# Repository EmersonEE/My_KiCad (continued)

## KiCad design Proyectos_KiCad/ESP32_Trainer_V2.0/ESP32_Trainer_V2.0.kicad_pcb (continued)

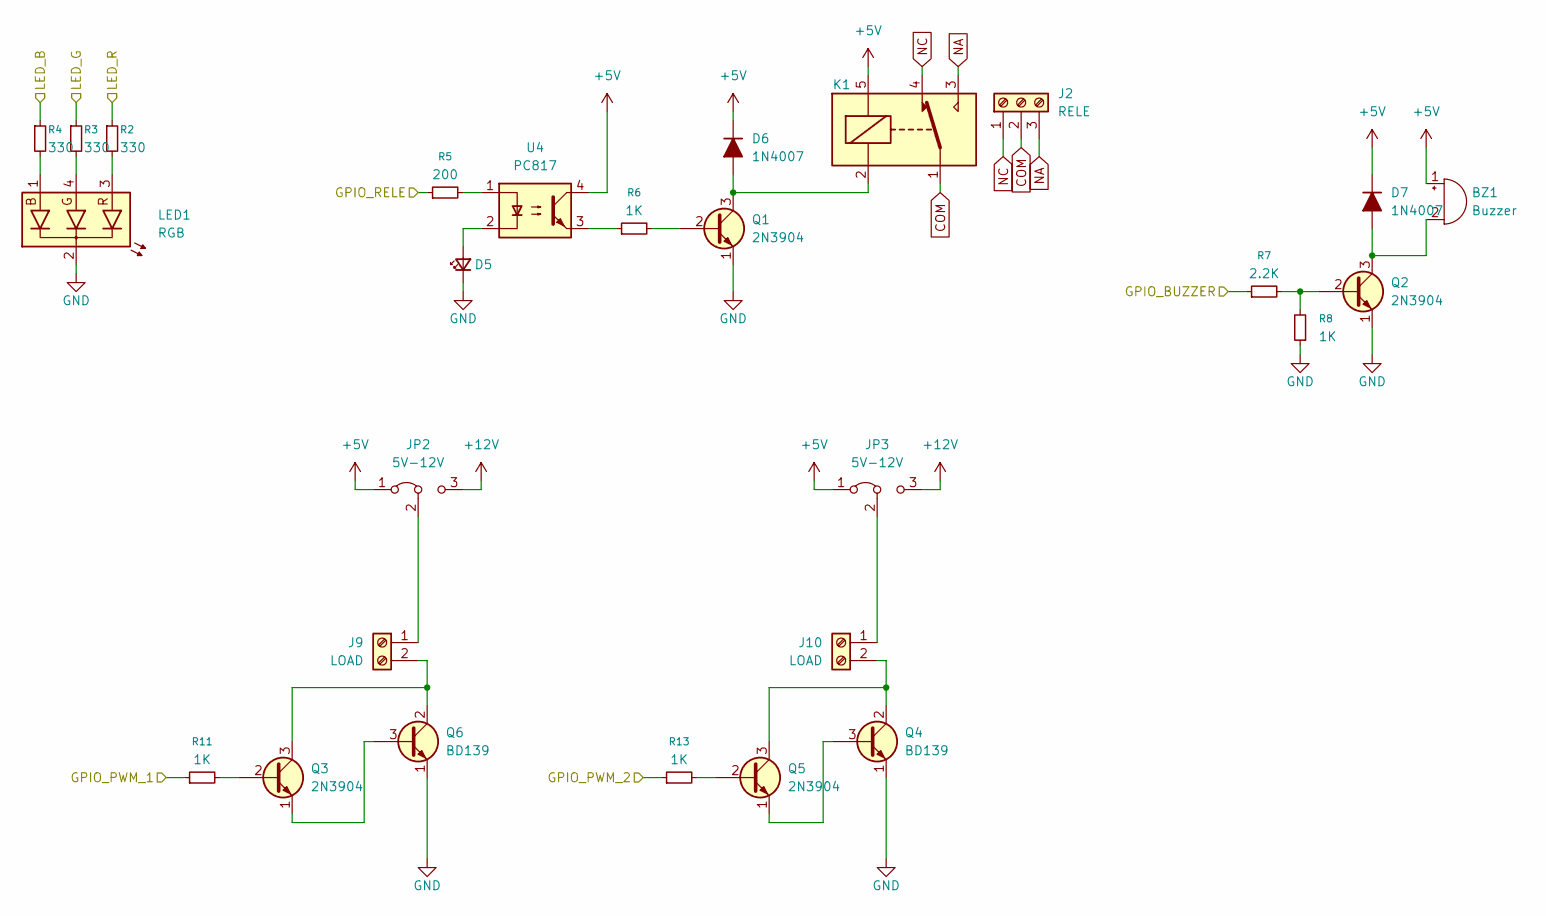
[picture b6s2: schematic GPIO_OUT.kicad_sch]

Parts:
BZ1: Buzzer; Buzzer_12x9.5RM7.6
D5: LED_OPTO; LED_D3.0mm
D6: 1N4007; D_DO-41_SOD81_P7.62mm_Horizontal
D7: 1N4007; D_SMA_BigPads
J2: RELE; TerminalBlock_Phoenix_MKDS-1,5-3-5.08_1x03_P5.08mm_Horizont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
J9, J10: LOAD; TerminalBlock_Phoenix_MKDS-1,5-2-5.08_1x02_P5.08mm_Horizont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
JP2, JP3: 5V-12V; PinHeader_1x03_P2.54mm_Vertical
K1: SANYOU_SRD_Form_C; Relay_SPDT_SANYOU_SRD_Series_Form_C
LED1: RGB; LED_D5.0mm-4_RGB_Wide_Pins
Q1, Q2, Q3, Q5: 2N3904; SOT-23W_BigPads
Q4, Q6: BD139; TO-126-3_Vertical_ECB
R2, R3, R4: 330; R_0805_2012Metric_Pad1.15x1.40mm
R5: 200; R_0805_2012Metric_Pad1.15x1.40mm
R6, R8, R11, R13: 1K; R_0805_2012Metric_Pad1.15x1.40mm
R7: 2.2K; R_0805_2012Metric_Pad1.15x1.40mm
U4: PC817; DIP-4_W7.62mm_LongPads

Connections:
+5V: BZ1.1 (+), D6.1 (K), D7.1 (K), JP2.1 (A), JP3.1 (A), K1.5, U4.4; also elsewhere on the board
+12V: JP2.3 (B), JP3.3 (B); also elsewhere on the board
/ESP32/GPIO_BUZZER: R7.1; also elsewhere on the board
/ESP32/GPIO_PWM_1: R11.1; also elsewhere on the board
/ESP32/GPIO_PWM_2: R13.1; also elsewhere on the board
/ESP32/GPIO_RELE: R5.1; also elsewhere on the board
/ESP32/LED_B: R4.1; also elsewhere on the board
/ESP32/LED_G: R3.1; also elsewhere on the board
/ESP32/LED_R: R2.1; also elsewhere on the board
COM: J2.2, K1.1
GND: D5.1 (K), LED1.2 (A), Q1.1 (E), Q2.1 (E), Q4.1 (E), Q6.1 (E), R8.1; also elsewhere on the board
NA: J2.3, K1.3
NC: J2.1, K1.4
unnamed: BZ1.2 (-), D7.2 (A), Q2.3 (C)
unnamed: D5.2 (A), U4.2
unnamed: D6.2 (A), K1.2, Q1.3 (C)
unnamed: J9.1, JP2.2 (C)
unnamed: J9.2, Q3.3 (C), Q6.2 (C)
unnamed: J10.1, JP3.2 (C)
unnamed: J10.2, Q4.2 (C), Q5.3 (C)
unnamed: LED1.1 (B), R4.2
unnamed: LED1.4 (G), R3.2
unnamed: LED1.3 (R), R2.2
unnamed: Q1.2 (B), R6.2
unnamed: Q2.2 (B), R7.2, R8.2
unnamed: Q3.2 (B), R11.2
unnamed: Q3.1 (E), Q6.3 (B)
unnamed: Q4.3 (B), Q5.1 (E)
unnamed: Q5.2 (B), R13.2
unnamed: R5.2, U4.1
unnamed: R6.1, U4.3

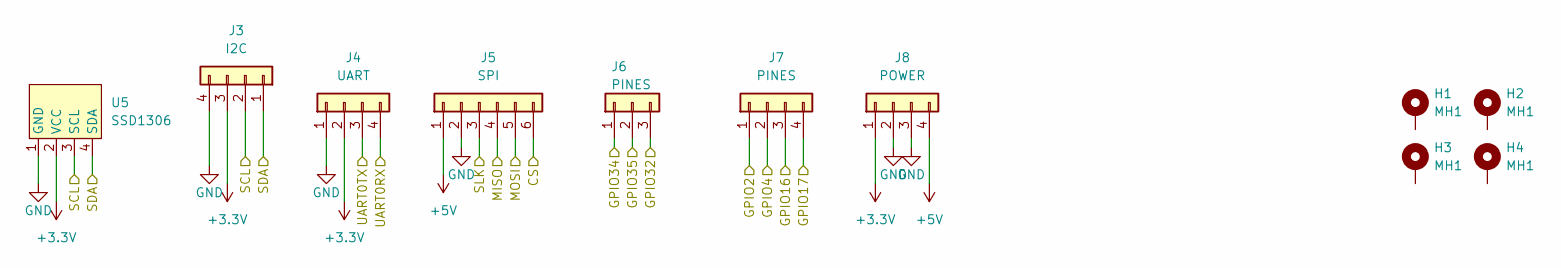
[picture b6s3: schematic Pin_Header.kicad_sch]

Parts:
H1, H2, H3, H4: MH1; MountingHole_3.2mm_M3_Pad_Via
J3: I2C; PinHeader_1x04_P2.54mm_Horizontal
J4: UART; PinHeader_1x04_P2.54mm_Vertical
J5: SPI; PinHeader_1x06_P2.54mm_Vertical
J6: PINES; PinHeader_1x03_P2.54mm_Vertical
J7: PINES; PinHeader_1x04_P2.54mm_Vertical
J8: POWER; PinHeader_1x04_P2.54mm_Vertical
U5: SSD1306

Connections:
+3.3V: J3.3, J4.2, J8.1, U5.2 (VCC); also elsewhere on the board
+5V: J5.1, J8.4; also elsewhere on the board
/ESP32/CLK: J5.3; also elsewhere on the board
/ESP32/CS: J5.6; also elsewhere on the board
/ESP32/GPIO2: J7.1; also elsewhere on the board
/ESP32/GPIO4: J7.2; also elsewhere on the board
/ESP32/GPIO16: J7.3; also elsewhere on the board
/ESP32/GPIO17: J7.4; also elsewhere on the board
/ESP32/GPIO32: J6.3; also elsewhere on the board
/ESP32/GPIO34: J6.1; also elsewhere on the board
/ESP32/GPIO35: J6.2; also elsewhere on the board
/ESP32/MISO: J5.4; also elsewhere on the board
/ESP32/MOSI: J5.5; also elsewhere on the board
/ESP32/SCL: J3.2, U5.3 (SCL); also elsewhere on the board
/ESP32/SDA: J3.1, U5.4 (SDA); also elsewhere on the board
/ESP32/UART0RX: J4.4; also elsewhere on the board
/ESP32/UART0TX: J4.3; also elsewhere on the board
GND: J3.4, J4.1, J5.2, J8.2, J8.3, U5.1 (GND); also elsewhere on the board

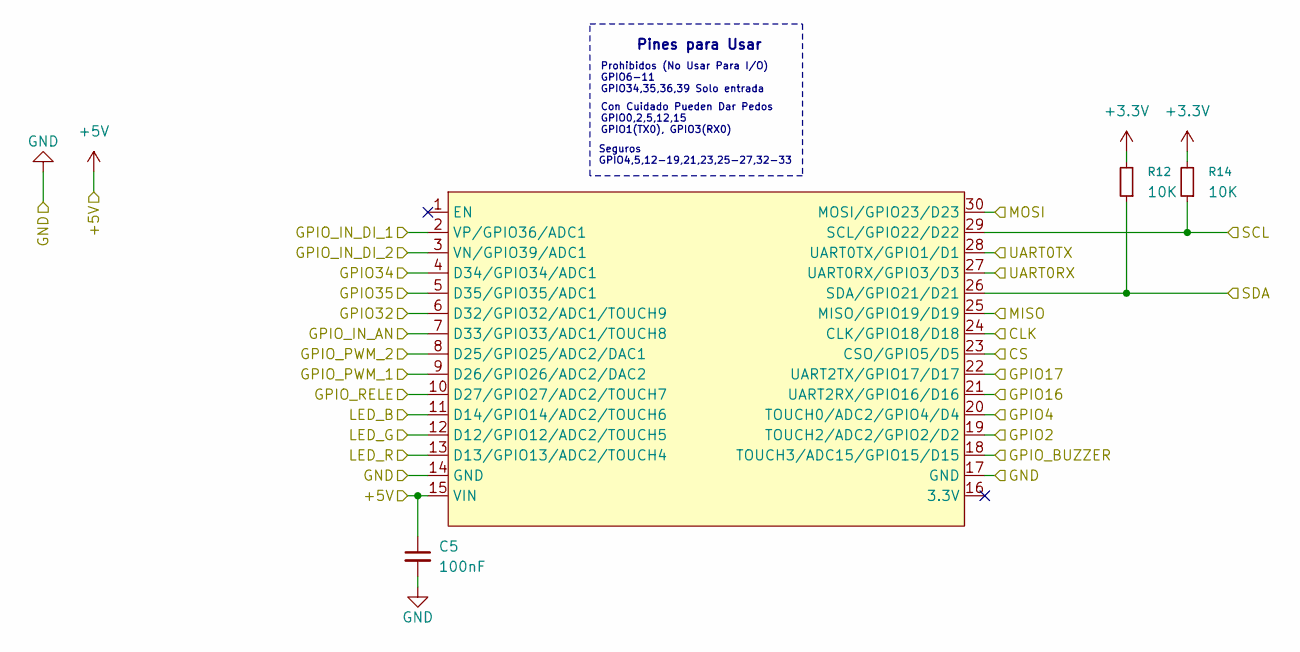
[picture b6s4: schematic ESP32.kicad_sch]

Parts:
C5: 100nF; C_Disc_D4.3mm_W1.9mm_P5.00mm
R12, R14: 10K; R_0805_2012Metric_Pad1.15x1.40mm
U3: ESP32_DevKit_V1_DOIT; ESP32_DEVKIT_V1_E32

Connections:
+3.3V: R12.2, R14.2; also elsewhere on the board
+5V: C5.1, U3.15 (VIN); also elsewhere on the board
/ESP32/CLK: U3.24 (CLK/GPIO18/D18); also elsewhere on the board
/ESP32/CS: U3.23 (CSO/GPIO5/D5); also elsewhere on the board
/ESP32/GPIO2: U3.19 (TOUCH2/ADC2/GPIO2/D2); also elsewhere on the board
/ESP32/GPIO4: U3.20 (TOUCH0/ADC2/GPIO4/D4); also elsewhere on the board
/ESP32/GPIO16: U3.21 (UART2RX/GPIO16/D16); also elsewhere on the board
/ESP32/GPIO17: U3.22 (UART2TX/GPIO17/D17); also elsewhere on the board
/ESP32/GPIO32: U3.6 (D32/GPIO32/ADC1/TOUCH9); also elsewhere on the board
/ESP32/GPIO34: U3.4 (D34/GPIO34/ADC1); also elsewhere on the board
/ESP32/GPIO35: U3.5 (D35/GPIO35/ADC1); also elsewhere on the board
/ESP32/GPIO_BUZZER: U3.18 (TOUCH3/ADC15/GPIO15/D15); also elsewhere on the board
/ESP32/GPIO_IN_AN: U3.7 (D33/GPIO33/ADC1/TOUCH8); also elsewhere on the board
/ESP32/GPIO_IN_DI_1: U3.2 (VP/GPIO36/ADC1); also elsewhere on the board
/ESP32/GPIO_IN_DI_2: U3.3 (VN/GPIO39/ADC1); also elsewhere on the board
/ESP32/GPIO_PWM_1: U3.9 (D26/GPIO26/ADC2/DAC2); also elsewhere on the board
/ESP32/GPIO_PWM_2: U3.8 (D25/GPIO25/ADC2/DAC1); also elsewhere on the board
/ESP32/GPIO_RELE: U3.10 (D27/GPIO27/ADC2/TOUCH7); also elsewhere on the board
/ESP32/LED_B: U3.11 (D14/GPIO14/ADC2/TOUCH6); also elsewhere on the board
/ESP32/LED_G: U3.12 (D12/GPIO12/ADC2/TOUCH5); also elsewhere on the board
/ESP32/LED_R: U3.13 (D13/GPIO13/ADC2/TOUCH4); also elsewhere on the board
/ESP32/MISO: U3.25 (MISO/GPIO19/D19); also elsewhere on the board
/ESP32/MOSI: U3.30 (MOSI/GPIO23/D23); also elsewhere on the board
/ESP32/SCL: R14.1, U3.29 (SCL/GPIO22/D22); also elsewhere on the board
/ESP32/SDA: R12.1, U3.26 (SDA/GPIO21/D21); also elsewhere on the board
/ESP32/UART0RX: U3.27 (UART0RX/GPIO3/D3); also elsewhere on the board
/ESP32/UART0TX: U3.28 (UART0TX/GPIO1/D1); also elsewhere on the board
GND: C5.2, U3.14 (GND), U3.17 (GND); also elsewhere on the board

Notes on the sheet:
Pines para Usar
Con Cuidado Pueden Dar Pedos GPIO0,2,5,12,15 GPIO1(TX0), GPIO3(RX0)
Prohibidos (No Usar Para I/O) GPIO6-11 GPIO34,35,36,39 Solo entrada
Seguros GPIO4,5,12-19,21,23,25-27,32-33

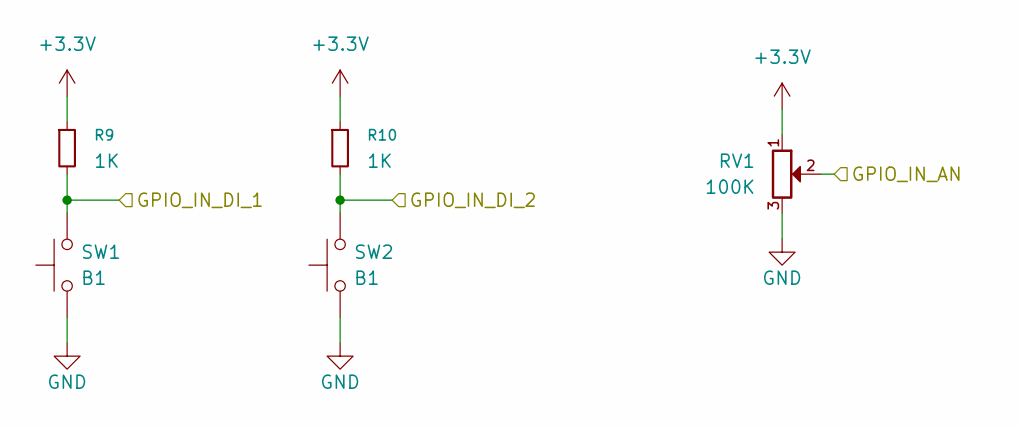
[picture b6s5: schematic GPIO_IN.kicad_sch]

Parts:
R9, R10: 1K; R_0805_2012Metric_Pad1.15x1.40mm
RV1: 100K; Potentiometer_Bourns_3266Y_Vertical
SW1, SW2: B1; SW_PUSH_6mm

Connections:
+3.3V: R9.1, R10.1, RV1.1; also elsewhere on the board
/ESP32/GPIO_IN_AN: RV1.2; also elsewhere on the board
/ESP32/GPIO_IN_DI_1: R9.2, SW1.2; also elsewhere on the board
/ESP32/GPIO_IN_DI_2: R10.2, SW2.2; also elsewhere on the board
GND: RV1.3, SW1.1, SW2.1; also elsewhere on the board

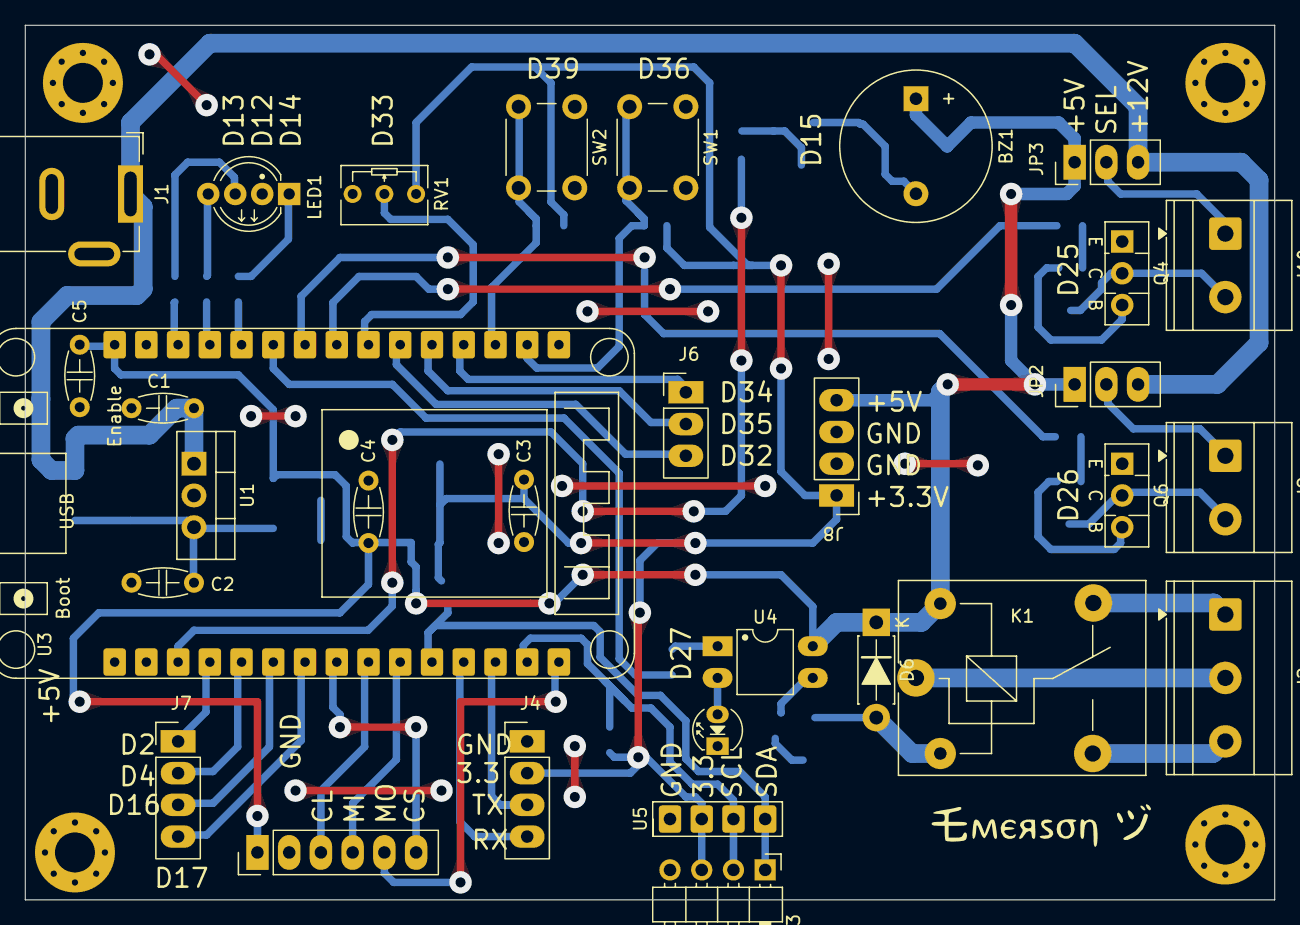
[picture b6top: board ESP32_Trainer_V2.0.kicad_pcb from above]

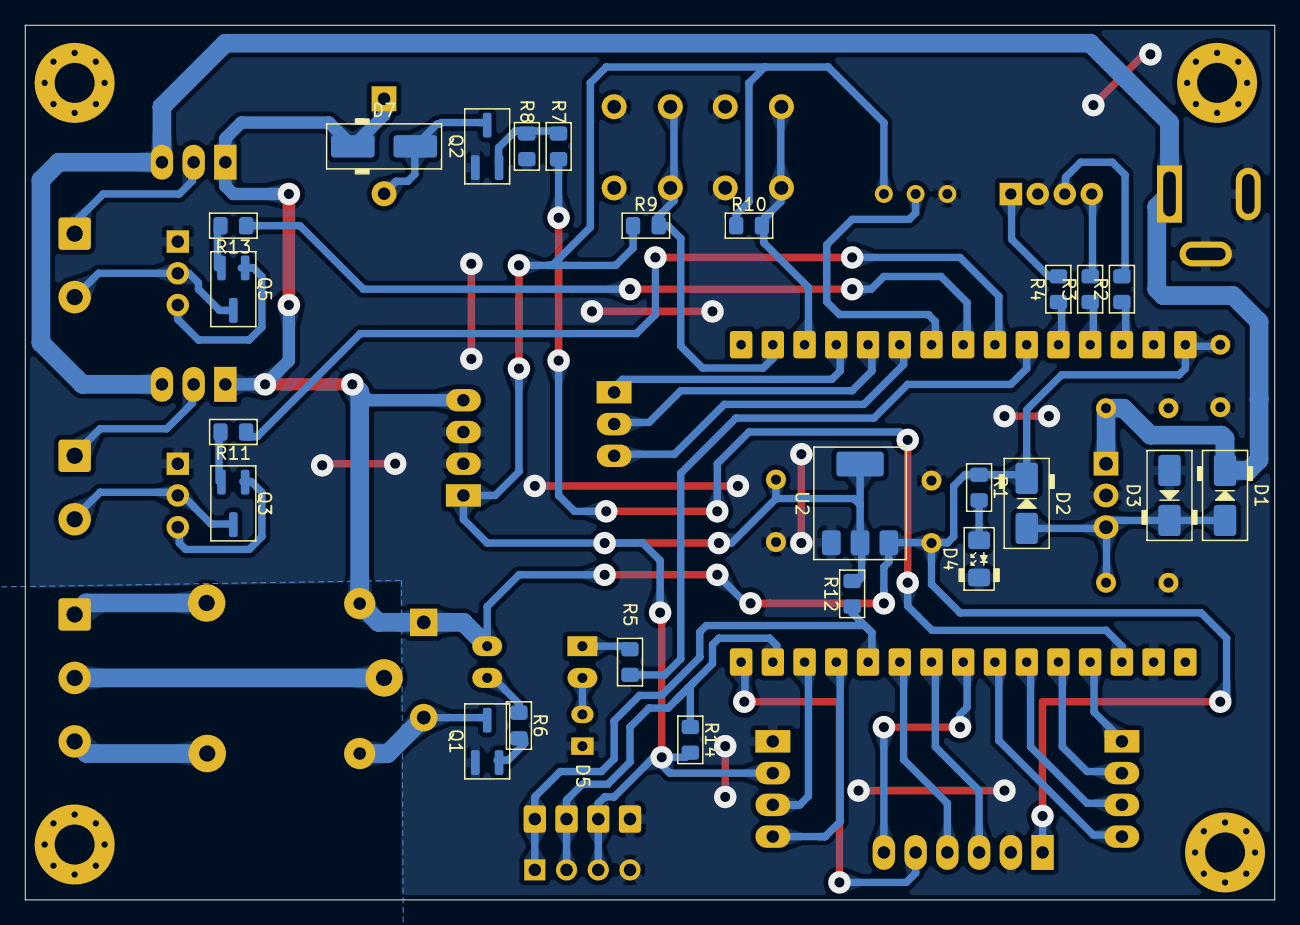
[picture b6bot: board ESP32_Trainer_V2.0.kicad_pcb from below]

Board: 2 copper layers, 100.0 x 70.0 mm, 59 parts (24 on the bottom side), 52 nets.

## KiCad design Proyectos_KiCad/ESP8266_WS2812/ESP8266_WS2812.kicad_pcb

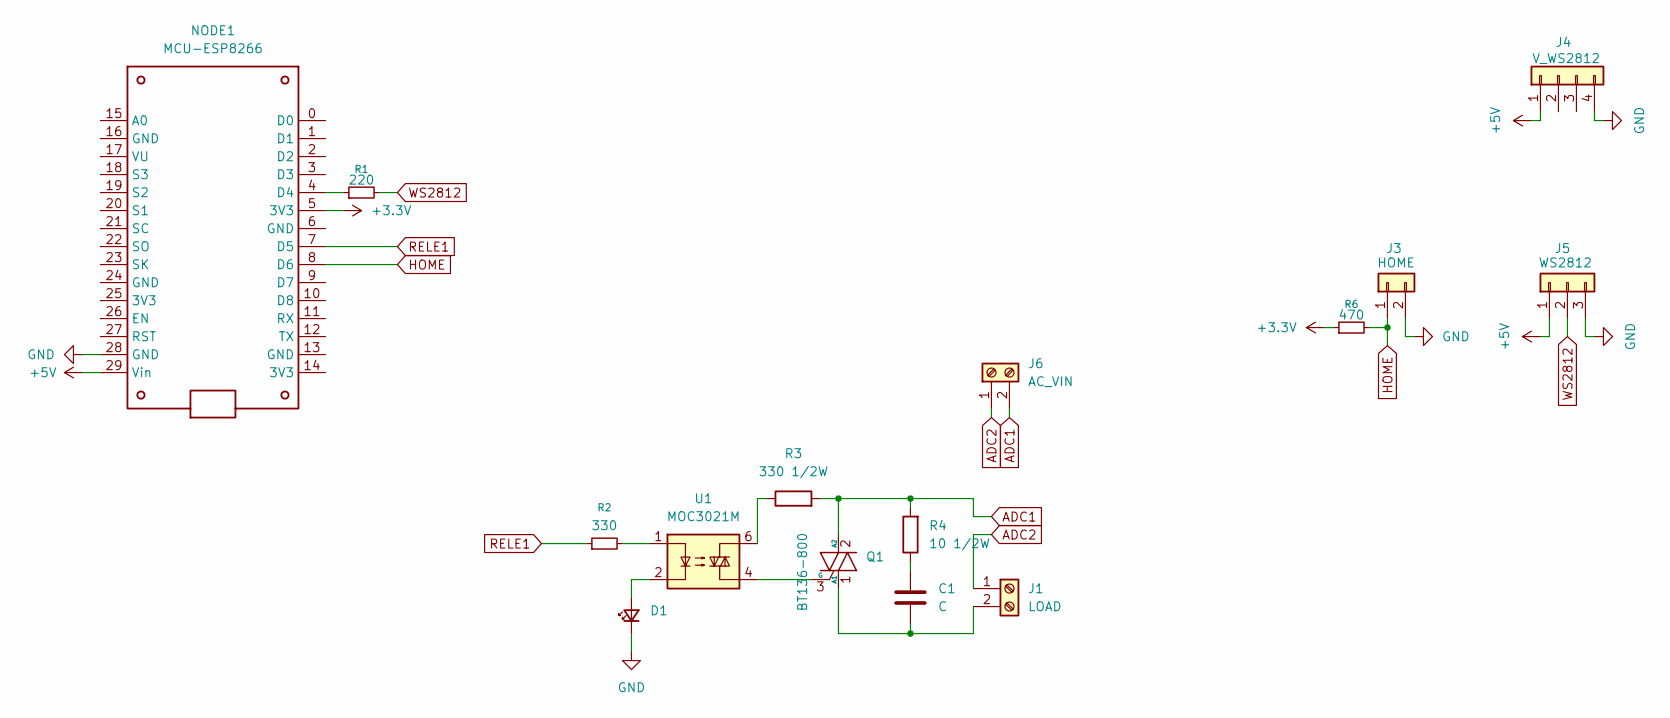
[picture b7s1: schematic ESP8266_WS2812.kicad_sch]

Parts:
C1: C; C_Rect_L13.0mm_W6.0mm_P10.00mm_FKS3_FKP3_MKS4
D1: LED_D5.0mm
J1: LOAD; TerminalBlock_Phoenix_MKDS-1,5-2-5.08_1x02_P5.08mm_Horizont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
J3: HOME; Molex_KK-254_AE-6410-02A_1x02_P2.54mm_Vertical
J4: V_WS2812; PinSocket_1x04_P2.54mm_Vertical
J5: WS2812; Molex_KK-254_AE-6410-03A_1x03_P2.54mm_Vertical
J6: AC_VIN; TerminalBlock_Phoenix_MKDS-1,5-2-5.08_1x02_P5.08mm_Horizont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
NODE1: MCU-ESP8266; NODEMCU-12E;NODEMCU-ESP8266
Q1: BT136-800; TO-220-3_VDC
R1: 220
R2: 330
R3: 330 1/2W; R_Axial_DIN0207_L6.3mm_D2.5mm_P10.16mm_Horizontal
R4: 10 1/2W; R_Axial_DIN0207_L6.3mm_D2.5mm_P15.24mm_Horizontal
R6: 470
U1: MOC3021M; MOC3020

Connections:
+3.3V: NODE1.5 (3V3), R6.1
+5V: J4.1, J5.1, NODE1.29 (Vin)
ADC1: J6.2, Q1.2 (A2), R3.2, R4.2
ADC2: J1.1, J6.1
GND: D1.1 (K), J3.2, J4.4, J5.3, NODE1.28 (GND)
HOME: J3.1, NODE1.8 (D6), R6.2
unnamed: C1.1, R4.1
unnamed: D1.2 (A), U1.2
unnamed: C1.2, J1.2, Q1.1 (A1)
unnamed: NODE1.4 (D4), R1.1
unnamed: Q1.3 (G), U1.4
unnamed: R2.2, U1.1
unnamed: R3.1, U1.6
RELE1: NODE1.7 (D5), R2.1
WS2812: J5.2, R1.2

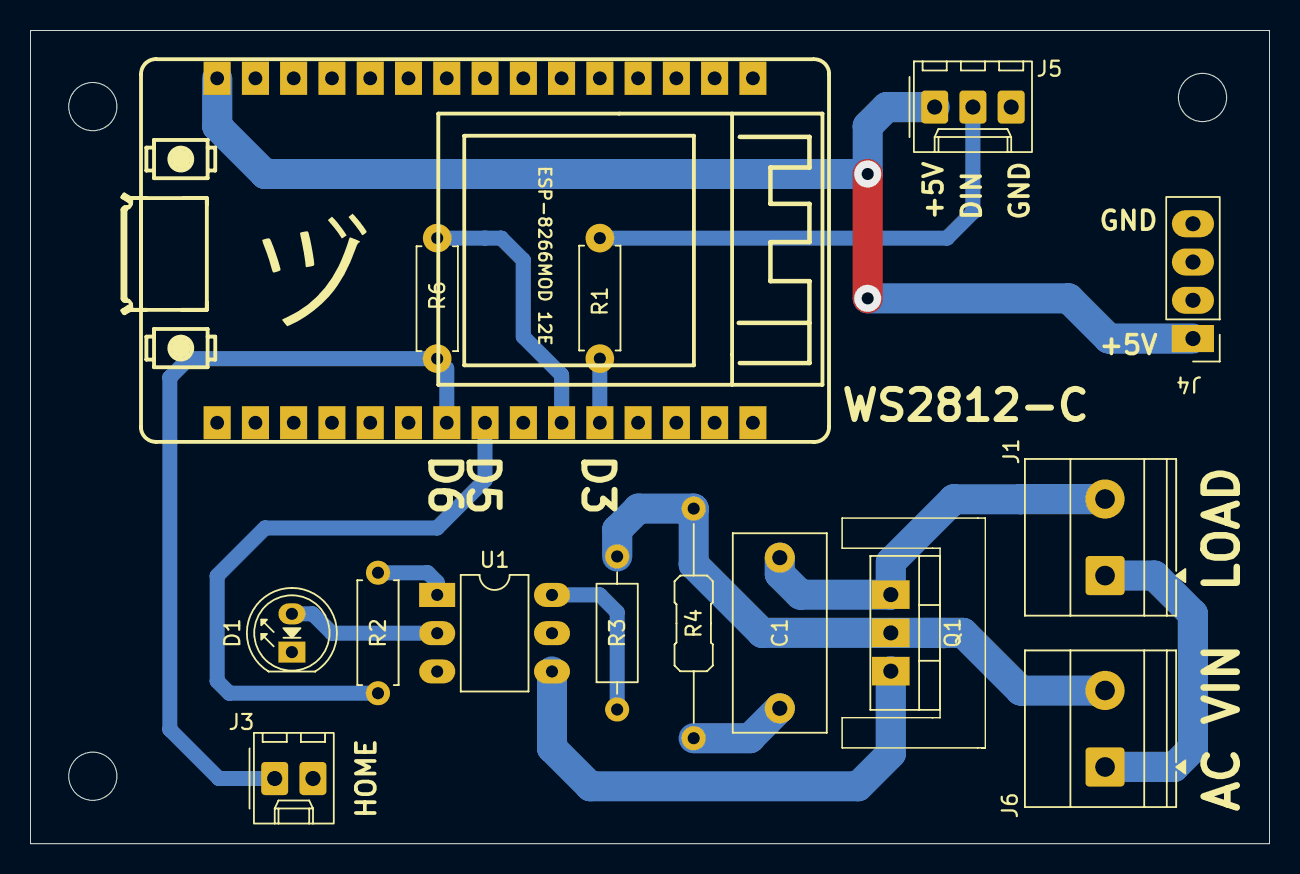
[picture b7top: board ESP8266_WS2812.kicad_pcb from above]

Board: 2 copper layers, 82.2 x 54.0 mm, 15 parts (0 on the bottom side), 15 nets.
